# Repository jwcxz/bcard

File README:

bcard

http://jwcxz.com/projects/bcard

bcard is an experimental attempt to make cheap electronic business card on a
thin PCB.  The main goals are for it to be:

    - cheap
    - not gaudy
    - not stupid
    
As awesome as it would be to make the card appear as a USB flash device that
contains my resume, that would be a bit too expensive.  One alternative, is
this design:

    http://www.instructables.com/id/USB-PCB-Business-Card/
    
But somebody already made it :) Other designs are much more expensive.

    http://mikepuchol.com/my-pcb-business-card/
    http://electronoblog.allanw.org/2011/08/yet-another-pcb-business-card-with-touchpad/
    http://www.youtube.com/watch?v=gSN2SAgYy7M
    http://www.chasingtrons.com/main/tag/business-card
    
My design incorporates a capacitive touch sensor with some blue LEDs around the
corners.  The blue LEDs are actually mounted upside-down so that the card
fluoresces.

Cost of parts is about $1.80 in quantities of 25 (at Digi-Key prices).  At
quantities of 100, the cost per board is $1.54.  The majority of the cost is in
the 4 LEDs and the microcontroller.  You can shave off a few cents by going
with an ATTiny4 instead of an ATTiny10.

IDK, it's cute.

Software Used:
    Board Design: Kicad     http://kicad.sf.net
                  Inkscape  http://inkscape.org
    Firwmare:     AVRA      http://avra.sf.net
                  AVRDUDE   http://www.nongnu.org/avrdude/

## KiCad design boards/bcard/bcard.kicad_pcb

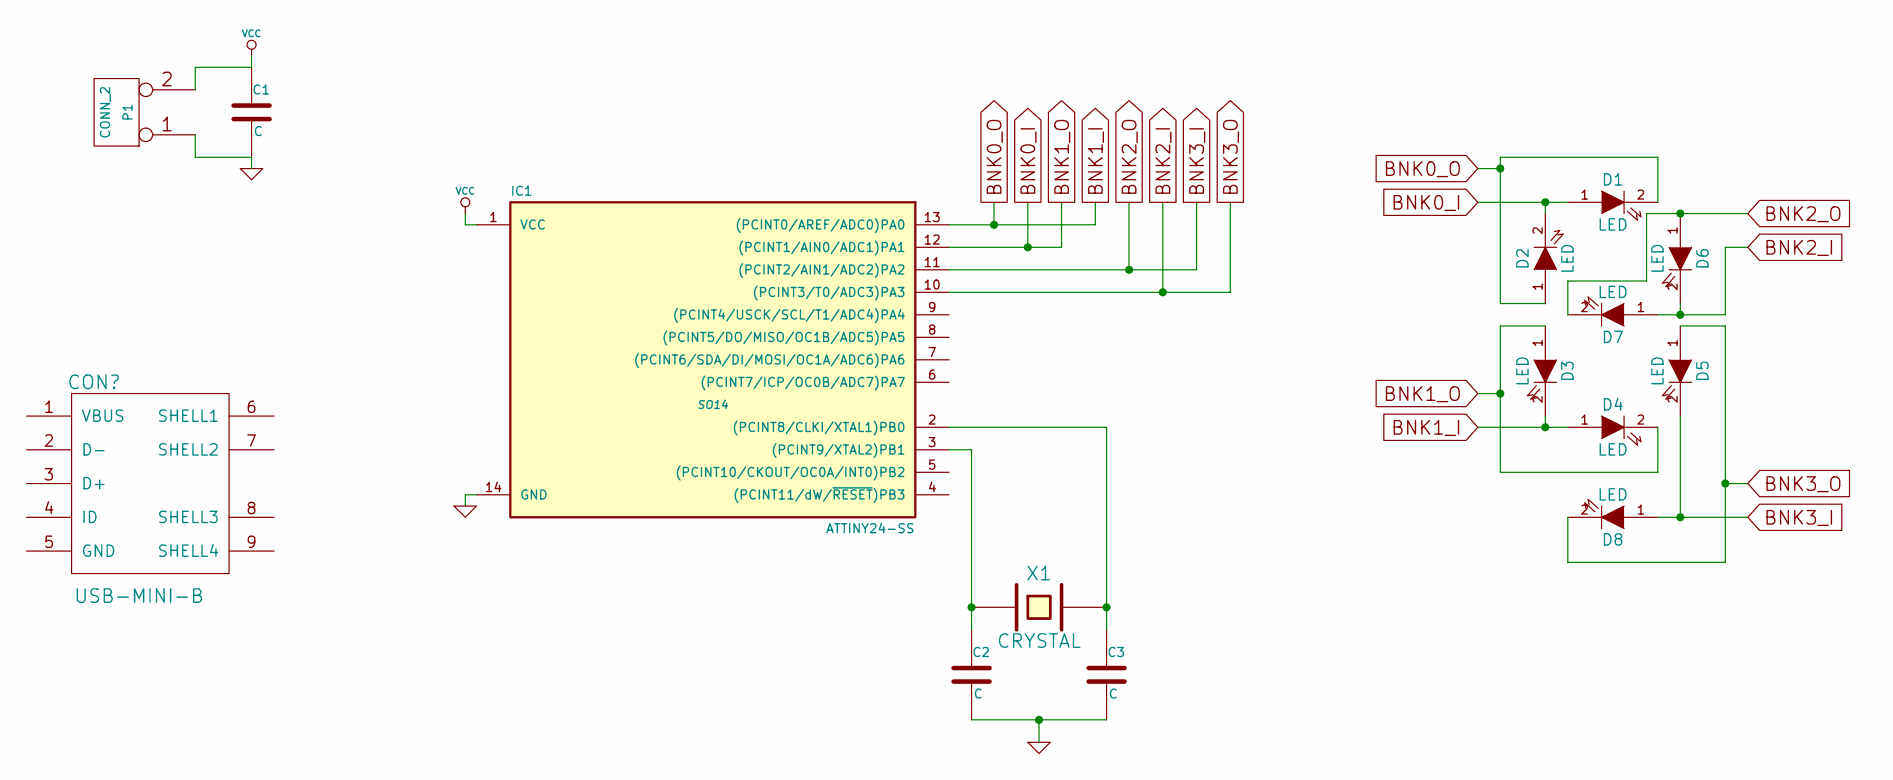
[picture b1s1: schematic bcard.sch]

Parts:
C1, C2, C3: C
D1, D2, D3, D4, D5, D6, D7, D8: LED
IC1: ATTINY24-SS; SO14
P1: CONN_2
X1: CRYSTAL

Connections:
BNK0_I: D1.1 (A), D2.2 (K), D3.1 (A), D4.2 (K), IC1.12 ((PCINT1/AIN0/ADC1)PA1)
BNK0_O: D1.2 (K), D2.1 (A), D3.2 (K), D4.1 (A), IC1.13 ((PCINT0/AREF/ADC0)PA0)
BNK2_I: D5.1 (A), D6.2 (K), D7.1 (A), D8.2 (K), IC1.10 ((PCINT3/T0/ADC3)PA3)
BNK2_O: D5.2 (K), D6.1 (A), D7.2 (K), D8.1 (A), IC1.11 ((PCINT2/AIN1/ADC2)PA2)
GND: C1.2, C2.2, C3.2, IC1.14 (GND), P1.1
unnamed: C3.1, IC1.2 ((PCINT8/CLKI/XTAL1)PB0), X1.2
unnamed: C2.1, IC1.3 ((PCINT9/XTAL2)PB1), X1.1
VCC: C1.1, IC1.1 (VCC), P1.2 (PM)

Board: 2 copper layers, 14 parts (0 on the bottom side), 8 nets, no tracks yet.

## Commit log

2012-03-02 readme draft
2012-03-04 started board
2012-03-06 added some qr codes, playing around with various ideas
2012-03-06 started
2012-03-08 boardwork
2012-03-09 first attempt at a layout -- very rough
2012-03-10 working on layout
2012-03-12 blah
2012-03-28 added second design svg
2012-03-29 first potential design ready -- needs etching
2012-03-29 first pcb design basically done
2012-04-03 added list of software used to README
2012-04-06 changed outer track widths to 20 mils for more reliable etching.
2012-04-22 working on new board design
2012-05-25 attempt at modified LEDs
2012-05-28 almost done with new style
2012-05-28 finished next revision of bcard -- ready to etch
2012-05-28 updated some pics of it
2012-05-30 revision 1.2 ready for etching -- uses a battery clip and side-oriented LEDs
2012-06-08 cleaned up board for etching -- successful etch confirmed
2012-06-10 3rd design export -- I really need to create a makefile for this...
2012-06-19 added attiny10 breakout board
2012-07-08 now that the dasaftdi programmer works, reorganized sourcecode and built a new makefile
2012-07-10 whoops, that was supposed to be SOT23 for the transistor, not SOT323
2012-07-11 added breakout board for the cap sensor -- maybe we need to make it thinner traces
2012-07-11 atmega testing framework for capacitive sensing algos built
2012-07-14 added atmega test code so far... very very messy
2012-07-15 added a couple of test patterns in preparation for complete board redesign
2012-07-16 first pass at an averaging algo... does not work
2012-07-21 added second csense idea
2012-07-21 added third possible design
2012-07-22 trying the derpy floating pin sensor board :/
2012-07-27 hopefully the actual final version of the sensor test -- uses double sided board to achieve floating pins
2012-07-28 revision of double layer sensor board test
2012-07-28 working algorithm for sensing (no power management)
2012-07-28 reminder for when I do the attiny code
2012-07-28 new swipe sensor for final bcard layout
2012-07-29 switching to dual layer board
    schematics and netlist are correct (and even annotated!)
    board layout needs serious work
    sensor might change a little bit
    gahhhhhhhhhhhhhhhhhh
2012-08-05 came up with roughly a final algorithm on the atmega
2012-08-05 final front imprint almost there
2012-08-05 started work on attiny code
    csense.asm is mostly working -- just needs a training phase
2012-08-05 training phase code written
2012-08-05 csense.asm working! successfully trains and measures presses
2012-08-05 cleaned up csense.asm, bcard.asm does its thing correctly (needs pwm)
2012-08-06 basic algo working -- needs some tweaking, pin reassignment, and power optimization
2012-08-07 code cleanup in preparation for pin switch
2012-08-14 added test of conformal coating
2013-09-21 begin new phase of bcard design -- two factor auth
